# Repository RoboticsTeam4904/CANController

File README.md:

### CANController
This is a KiCAD file for a PCB that converts the serial bus data from sensors to CAN bus data using an intermediary embedded Teensy 3.2 which are then passed through DB15 connectors and VGA cables to other similar PCBs (other board schematics can be found in different repositories on github.com/roboticsteam4904).
The main sensors are LiDAR and encoders but it can be used with most sensors that have more than 5-pin connections. It also functions as power and data signal for LED strips scuh as the Adafruit Neopixels.

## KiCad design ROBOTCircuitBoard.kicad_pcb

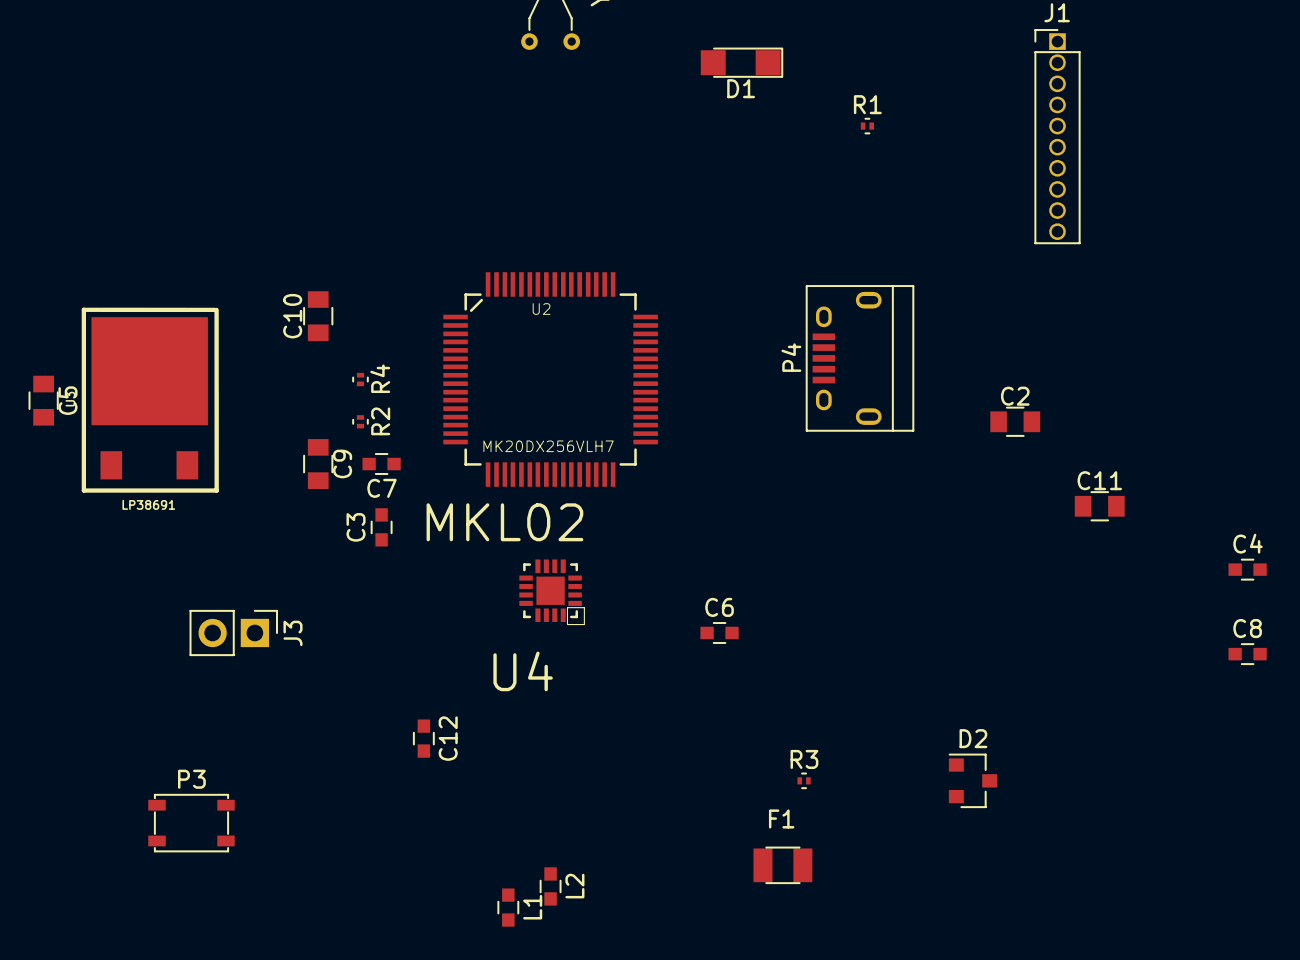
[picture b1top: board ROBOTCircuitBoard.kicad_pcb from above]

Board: 2 copper layers, 28 parts (0 on the bottom side), 34 nets, no tracks yet.

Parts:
C2, C5, C10, C11: 2.2uF; C_0805
C3, C7, C12: CP 0.1uF; C_0603
C4, C6, C8: 0.1uF; C_0603
C9: CP 2.2uF; C_0805
D1: LED; LED_1206
D2: D_Schottky_AAK; D_SOT-23_ANK
F1: Fuse; Fuse_SMD1206_Reflow
J1: Analog 9-0; Socket_Strip_Straight_1x10_Pitch1.27mm
J3: CONN_01X02; Pin_Header_Straight_1x02_Pitch2.54mm
L1, L2: L Ferrite; C_0603
P3: Pushbutton NO; SW_SPST_PTS810
P4: USB_OTG; USB_Micro-B
R1, R2: 470; R_0201
R3, R4: 33; R_0201
U2: MK20DX256VLH7; QFP50P1200X1200X160-64N
U3: LP38691; lp38691
U4: MKL02; Teensy_DIY_v1.0-QFN50P300X300X100-17N
Y1: Crystal 16MHz; Crystal_AT310_d3.0mm_l10.0mm_Horizontal

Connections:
+3V3: C11.1, D2.2, L2.1, U2.3, U2.7, U2.30, U2.48, U4.1
/AGND: C3.2, C7.2, C9.2, L1.1, U2.15, U2.16
/AREF: C7.1, R2.2, U2.14
/C0: U2.25, U4.8
/C1: U2.22, U4.7
/C2: U2.24, U4.9
/C3: P4.4, U2.23, U4.6
/M: P4.2, R4.2
/P: P4.3, R3.2
/RESET: U2.34, U4.4, U4.13
/VBAT: C12.1, U2.21
/VIN: C5.2, J3.2, U3.1
/VUSB: C2.2, F1.2, P4.1
GND: C2.1, C4.2, C5.1, C6.2, C8.2, C10.2, C11.2, C12.2, L1.2, P3.2, P4.5, P4.6, R1.2, U2.4, U2.31, U2.47, U3.2, U4.2
unnamed: C3.1, U2.17
unnamed: C9.1, L2.2, R2.1, U2.13
unnamed: D1.1, R1.1
unnamed: D1.2, U2.50
unnamed: F1.1, J3.1
unnamed: J1.1, U2.45
unnamed: J1.2, U2.44
unnamed: J1.3, U2.63
unnamed: J1.4, U2.62
unnamed: J1.5, U2.37
unnamed: J1.6, U2.38
unnamed: J1.7, U2.36
unnamed: J1.8, U2.35
unnamed: J1.9, U2.43
unnamed: J1.10, U2.58
unnamed: P3.1, U4.10
unnamed: R3.1, U2.5
unnamed: R4.1, U2.6
unnamed: U2.55, Y1.1
unnamed: U2.56, Y1.2

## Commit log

2017-03-26 Connected main chip and bootloader
2017-03-26 Made that shitty footprint slightly better
2017-03-28 Added reference folder with images
2017-03-28 Last commit incorrect
2017-06-03 worked more on the teensy
2017-07-18 Labled a button
2017-07-18 added the crystals
2017-07-25 fixing things more
2017-07-25 Added more components
2017-07-31 Fixed standardization and other issues
    Made grounds point downwards for standardization
    Fixed an issue with AREF and AGND not being on either side of a capacitor
    Fixed some incorrectly placed traces and labels
2017-08-01 added the lp38691
2017-08-01 finished schematic draft 1
2017-08-02 Fixed capacitor, organization, and VIN issues Fixed issues with pins 4 and 5 on the LP38691 not being connected to 3.3VDC becuase of capacitor Took out long traces and reorganized Made a VIN trace fo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
2017-08-02 Added a basic README This README has info about the project, but nothing about our github procedures yet
2017-08-13 Added LED and renamed incorrectly named files Added an LED for debugging purposes Renamed ROBOTCircuitBoard.kicad_pcb to ROBOTCircuitBoard-not_embedded.kicad_pcb because it is the same as a previous 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
2017-08-13 Made the README better README now has subheader font where appropriate and has slight alterations to the phrasing and accuracy.
2017-08-13 Fixed font again Subheader font looked really weird so it was sized down yet again
2017-08-13 Why the heck does this bother me so much? The README looks half-decent now so I can die in peace. Thanks for hating me markdown.
2017-08-14 It's better now
2017-08-15 Began annotations and added dual shottkey Began annotation of schematic Added a two inpput one output shottkey diode instead of two diodes going to VBUS
2017-08-15 Replaced jumper with 1X02 connector Replaced jumper with 1X02 connector for ability to manually determine which voltage source to use (using an external jumper cable) in case of misaligned voltages
2017-08-29 isolated the teensy
2017-09-01 added footprint libraries
2017-09-01 made a lp38691 footprint
2017-09-22 added libraries
2017-09-29 finished the component libraries
2017-09-30 updated netlist, soread out objects
2017-10-07 moved something
2018-01-07 adding kicad screenshot of scematic
